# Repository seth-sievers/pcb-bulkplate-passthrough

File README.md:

# pcb-bulkplate-passthrough
A simple pcb &amp; pinheader combo to pass ematch wiring through a bulkplate with holes

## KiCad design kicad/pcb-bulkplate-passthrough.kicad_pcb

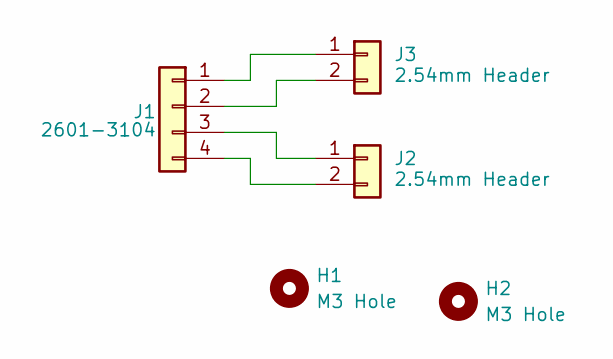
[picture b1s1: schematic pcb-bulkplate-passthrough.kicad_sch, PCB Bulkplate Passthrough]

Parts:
H1, H2: M3 Hole; MountingHole_3.2mm_M3
J1: 2601-3104; CONN4_2601-3104_WAG
J2, J3: 2.54mm Header; PinSocket_1x02_P2.54mm_Vertical

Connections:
unnamed: J1.1, J3.1
unnamed: J1.2, J3.2
unnamed: J1.3, J2.1
unnamed: J1.4, J2.2

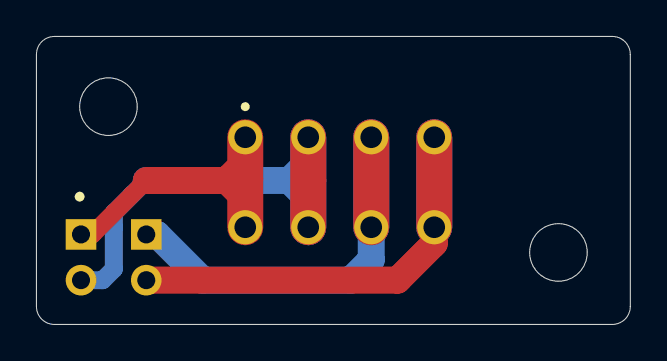
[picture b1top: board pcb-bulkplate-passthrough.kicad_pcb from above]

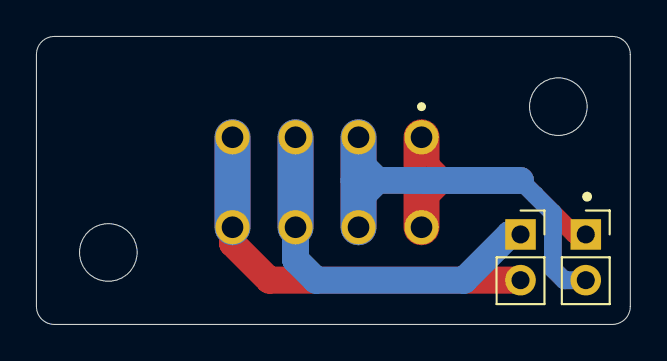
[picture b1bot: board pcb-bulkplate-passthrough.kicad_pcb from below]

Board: 2 copper layers, 33.0 x 16.0 mm, 5 parts (2 on the bottom side), 4 nets.

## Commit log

2025-09-13 done
2025-09-14 added 2 hole variant
